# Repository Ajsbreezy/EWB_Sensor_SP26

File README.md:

# EWB_Sensor_SP26
ESP32 controlled data collection in village of Malawi Africa.

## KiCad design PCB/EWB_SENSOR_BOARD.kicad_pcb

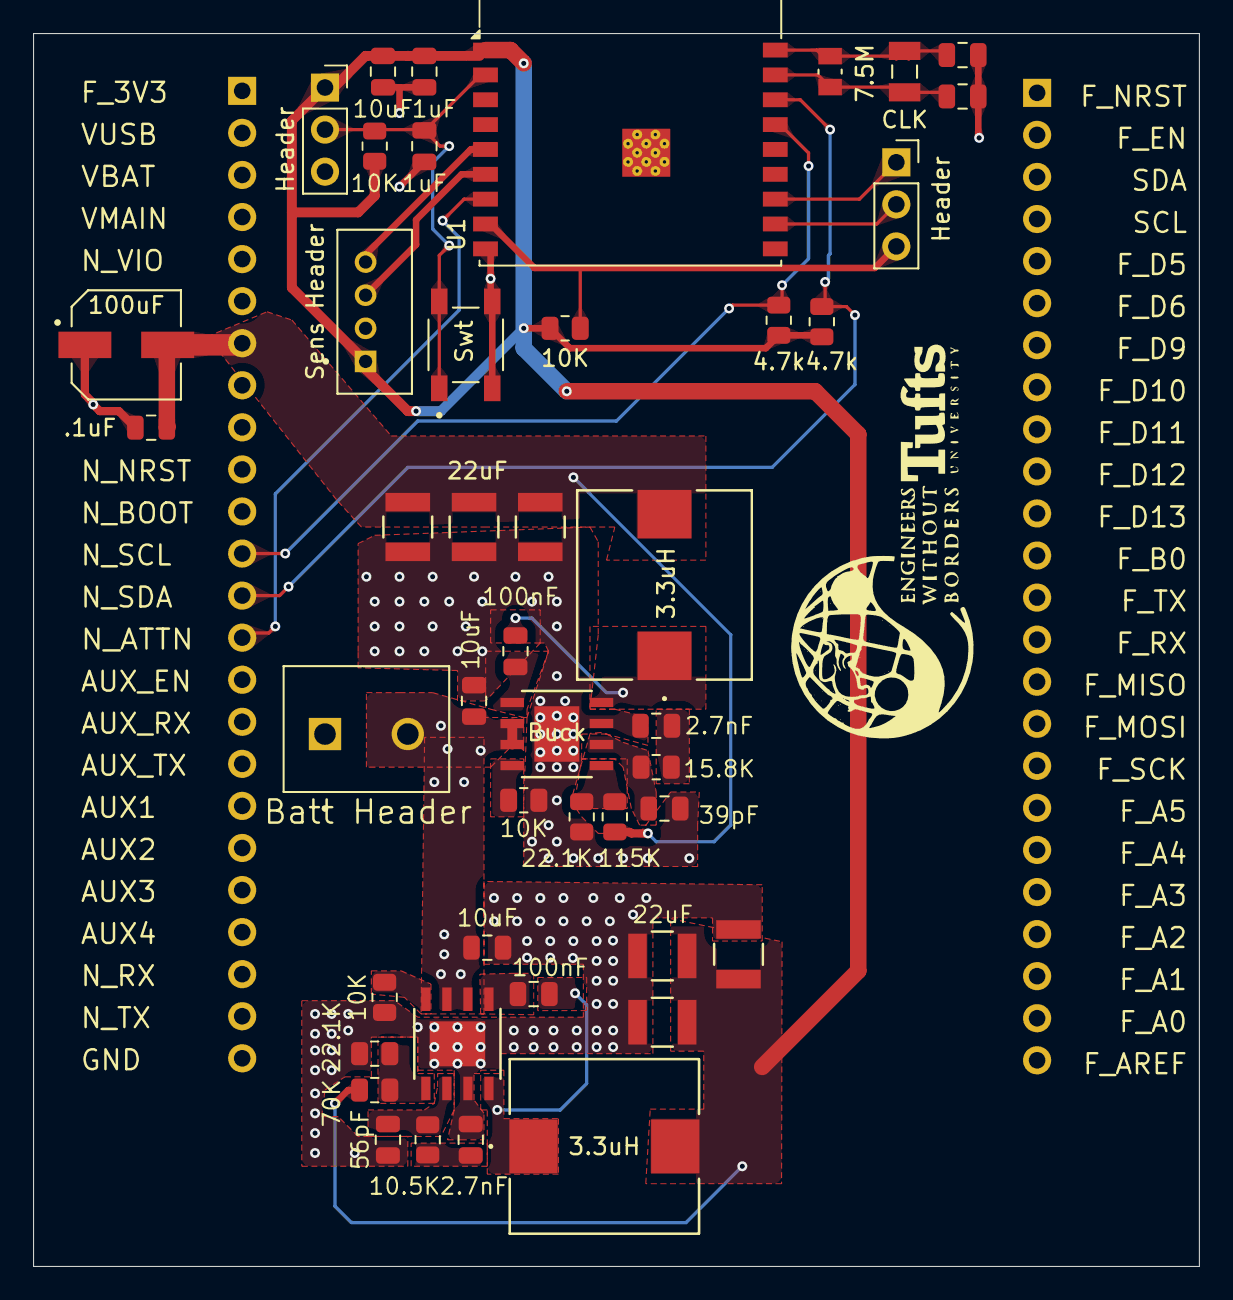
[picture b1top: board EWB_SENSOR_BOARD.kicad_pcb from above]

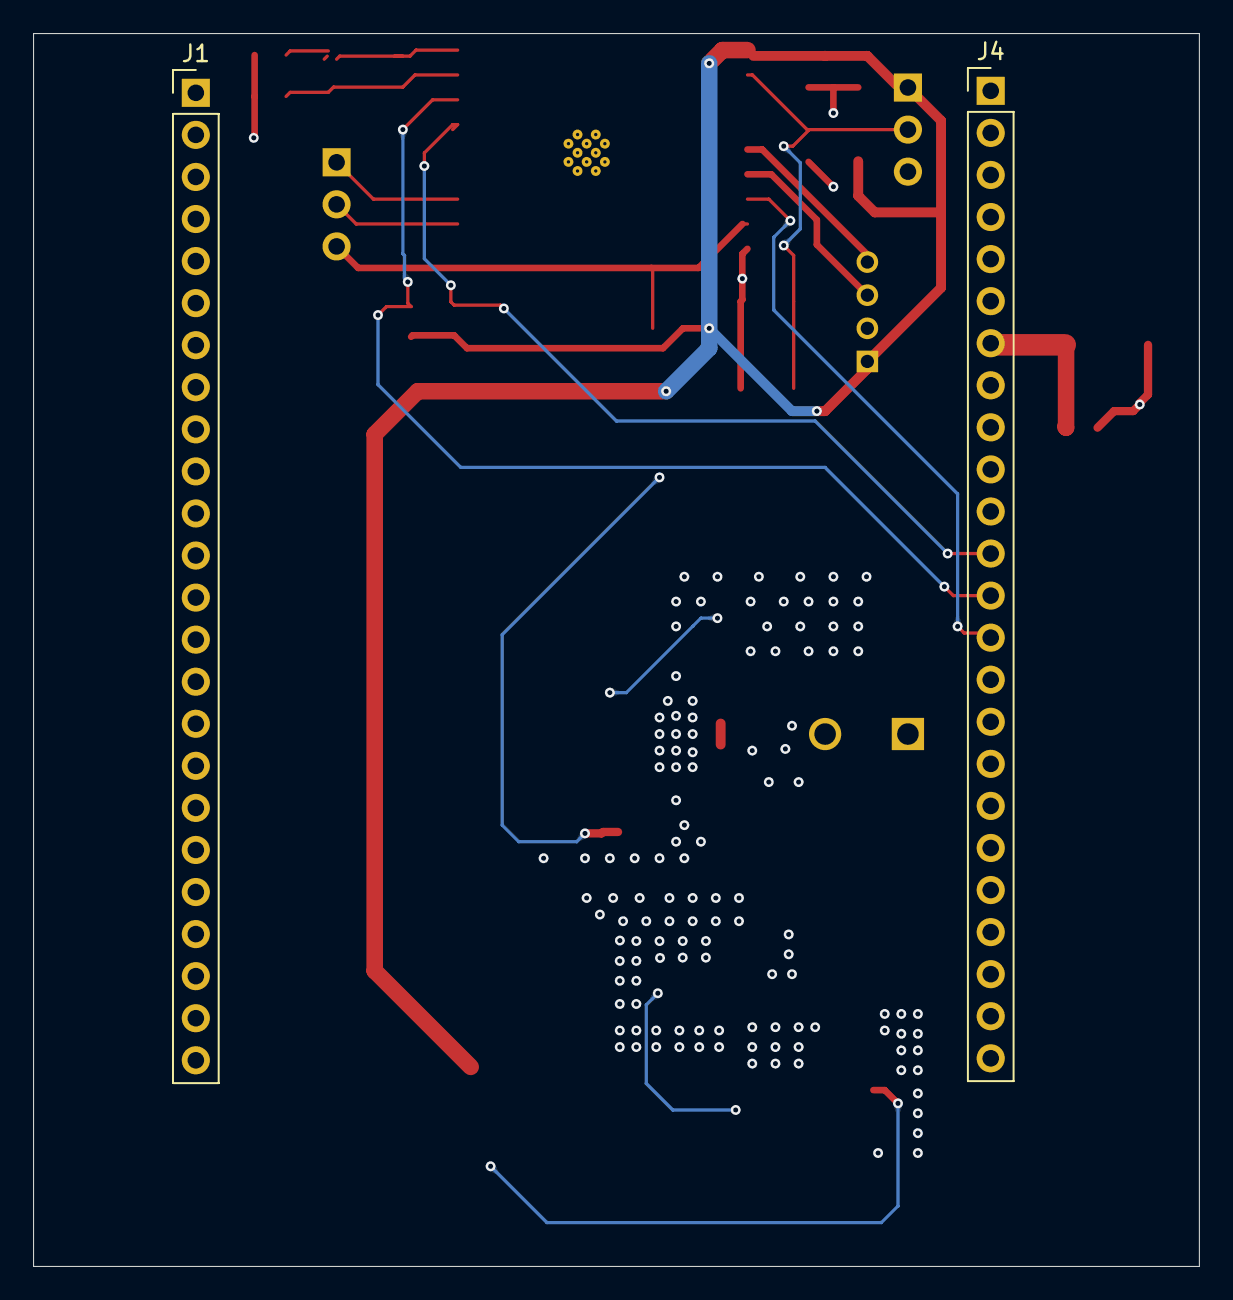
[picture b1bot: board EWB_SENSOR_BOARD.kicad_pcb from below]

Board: 4 copper layers, 70.4 x 74.5 mm, 47 parts (2 on the bottom side), 27 nets.

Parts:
1uF, 1uF#2: 1.0uF; C_0805_2012Metric
2.7nF, 2.7nF#2: 2.7nF; C_0805_2012Metric
3.3uH, 3.3uH#2: 3.3uH; IND_IHLP-4040DZ_VIS
4.7k, 4.7k#2: 4.7k; R_0805_2012Metric
7.5M: CR0805-JW-755ELF (7.5M); RESC2012X60N
10.5K: 10.5k; R_0805_2012Metric
10K, 10K#2, 10K#3, 10K#4: 10k; R_0805_2012Metric
10uF, 10uF#2, 10uF#3: 10.0uF; C_0805_2012Metric
15.8K: 15.8K; R_0805_2012Metric
22.1K, 22.1K#2: 22.1K; R_0805_2012Metric
22uF, 22uF#2: 22uF; CAP_CC1210_YAG
39pF: 39.0pF; C_0805_2012Metric
56pF: 56.0pF; C_0805_2012Metric
70K: 70k; R_0805_2012Metric
100nF, 100nF#2: 100.0nF; C_0805_2012Metric
100uF: 100uF; CAP_EEEFP1C101AP
115K: 115K; R_0805_2012Metric
.1uF: .1uF; C_0805_2012Metric
Batt Header: TB002-500-02BE; CUI_TB002-500-02BE
Buck: AP64500SP-13; SO-8EP_DIO
C6, C7: 15.0pF; C_0805_2012Metric
C13, C15, C19, C21: 22uF; CAP_CC1210_YAG
CLK: ABS07-32.768KHZ-T; XTAL_ABS07-32.768KHZ-T
Header: Conn_01x03_Pin; PinSocket_1x03_P2.54mm_Vertical
Header#2: Conn_01x03_Pin; PinSocket_1x03_P2.54mm_Vertical
J1, J4: Conn_01x24_Pin; PinHeader_1x24_P2.54mm_Vertical
Sens Header: B4B-PH-K-S; JST_B4B-PH-K-S
Swt: PTS_647_SM38_SMTR2_LFS; SW_PTS_647_SM38_SMTR2_LFS
U1: ESP32-C3-WROOM-02-N4; ESP32-C3-WROOM-02
U2: AP64500SP-13; SO-8EP_DIO

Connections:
+3.3V: 1uF.1, 3.3uH#2.2, 4.7k.1, 4.7k#2.1, 10K#2.2, 10K#4.1, 10uF#2.1, 22uF.2, 70K.2, C19.2, C21.2, Header#2.1, Sens Header.1, U1.1 (3V3)
+5V: 3.3uH.2, 22uF#2.2, 100uF.2, 115K.2, .1uF.2, C13.2, C15.2, J4.7
/12.8V: 10uF.2, 10uF#3.2, Batt Header.2, Buck.2 (VIN), Buck.3 (EN), U2.2 (VIN), U2.3 (EN)
/ESP_IO0: 10K#2.1, Header.3, U1.8 (IO9)
/ESP_RXD: Header.2, U1.11 (RXD)
/ESP_TXD: Header.1, U1.12 (TXD)
/FB: 22.1K.2, 115K.1, Buck.5 (FB)
/FB_1: 22.1K#2.2, 70K.1, U2.5 (FB)
/N_ATTN: J4.14, U1.7 (IO8)
/N_SCL: 4.7k#2.2, J4.12, U1.15 (IO3)
/N_SDA: 4.7k.2, J4.13, U1.16 (IO2)
/SNS_RX: Sens Header.4, U1.5 (IO6)
/SNS_TX: Sens Header.3, U1.6 (IO7)
/SW: 3.3uH.1, 100nF#2.2, Buck.8 (SW)
/SW_1: 3.3uH#2.1, 100nF.2, U2.8 (SW)
/XTAL_32K_N: 7.5M.2, C7.2, CLK.2, U1.17 (IO1)
/XTAL_32K_P: 7.5M.1, C6.2, CLK.1, U1.18 (IO0)
GND: 1uF.2, 1uF#2.1, 2.7nF.1, 2.7nF#2.1, 10K.1, 10K#3.1, 10uF.1, 10uF#2.2, 10uF#3.1, 22.1K.1, 22.1K#2.1, 22uF.1, 22uF#2.1, 39pF.1, 56pF.1, 100uF.1, .1uF.1, Batt Header.1, Buck.7 (GND), Buck.EPAD (GND), C6.1, C7.1, C13.1, C15.1, C19.1, C21.1, Header#2.3, J4.24, Sens Header.2, Swt.3, Swt.4, U1.9 (GND), U1.19 (GND__1), U2.7 (GND), U2.EPAD (GND)
unnamed: 2.7nF.2, 15.8K.1
unnamed: 2.7nF#2.2, 10.5K.1
unnamed: 100nF.1, U2.1 (BST)
unnamed: 10.5K.2, 56pF.2, U2.6 (COMP)
unnamed: 10K#3.2, U2.4 (RT/CLK)
unnamed: 100nF#2.1, Buck.1 (BST)
unnamed: 15.8K.2, 39pF.2, Buck.6 (COMP)
unnamed: 10K.2, Buck.4 (RT/CLK)
RESET: 1uF#2.2, 10K#4.2, Header#2.2, Swt.1, Swt.2, U1.2 (EN)

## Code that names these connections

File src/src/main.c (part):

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// WIRING / CONNECTOR PINOUT
//
//  Notecard (via Notecarrier header J1/J4, I2C):
//    N_SDA   -> ESP32-C3 GPIO2
//    N_SCL   -> ESP32-C3 GPIO3
//    N_ATTN  -> ESP32-C3 GPIO8  (optional, not used yet but there just in case)
//    4.7kΩ pull-ups on SDA and SCL to +3.3V (R9, R2 on PCB)
//
//  Ultrasonic Sensor (via J3, 4-pin JST PH, UART):
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#define NOTE_ATTN_PIN  8    // ESP32-C3 GPIO8 -> Notecard ATTN (for future use)

// UART to ultrasonic distance sensor
#define SNS_RX_PIN     6    // ESP32-C3 GPIO6 -> Sensor TX
#define SNS_TX_PIN     7    // ESP32-C3 GPIO7 -> Sensor RX

// defines
#define SLEEP_DURATION_US    3600000000ULL   // 1 hour in microseconds
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    uart_param_config(UART_NUM_1, &cfg);

    // set our pins (default pins)
    uart_set_pin(UART_NUM_1, SNS_TX_PIN, SNS_RX_PIN, UART_PIN_NO_CHANGE, 
        UART_PIN_NO_CHANGE);
}

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
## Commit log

2026-03-02 Project Directories
2026-03-09 V1 of Schematic ready to route
2026-03-12 Added Notecarrier footprint
2026-03-23 Changed LDO to buck, found capacitors and inductors, added bulk capacitance
2026-03-24 distance sensor + last sem old code
2026-04-06 almost finished
2026-04-06 Finished PCB?
2026-04-07 questionable code that worked...
    we need to review how it fully works and implement the new sensor code in
2026-04-07 Updated logReading function for improved clarity
2026-04-07 Final PCB
2026-04-07 updated parseJsonLong for clarity
2026-04-07 updated notecardCommand for clarity
2026-04-07 Created Nathan code
2026-04-07 added nathan's code
2026-04-07 Changed Silk Screen to include parts values
2026-04-14 combined comments, new sensor, rtc, no SD card
2026-05-02 Fixed and transitioned code to ESP-IDF Framework
2026-05-02 fixed some platform.io linker issues
2026-05-07 small fixes
